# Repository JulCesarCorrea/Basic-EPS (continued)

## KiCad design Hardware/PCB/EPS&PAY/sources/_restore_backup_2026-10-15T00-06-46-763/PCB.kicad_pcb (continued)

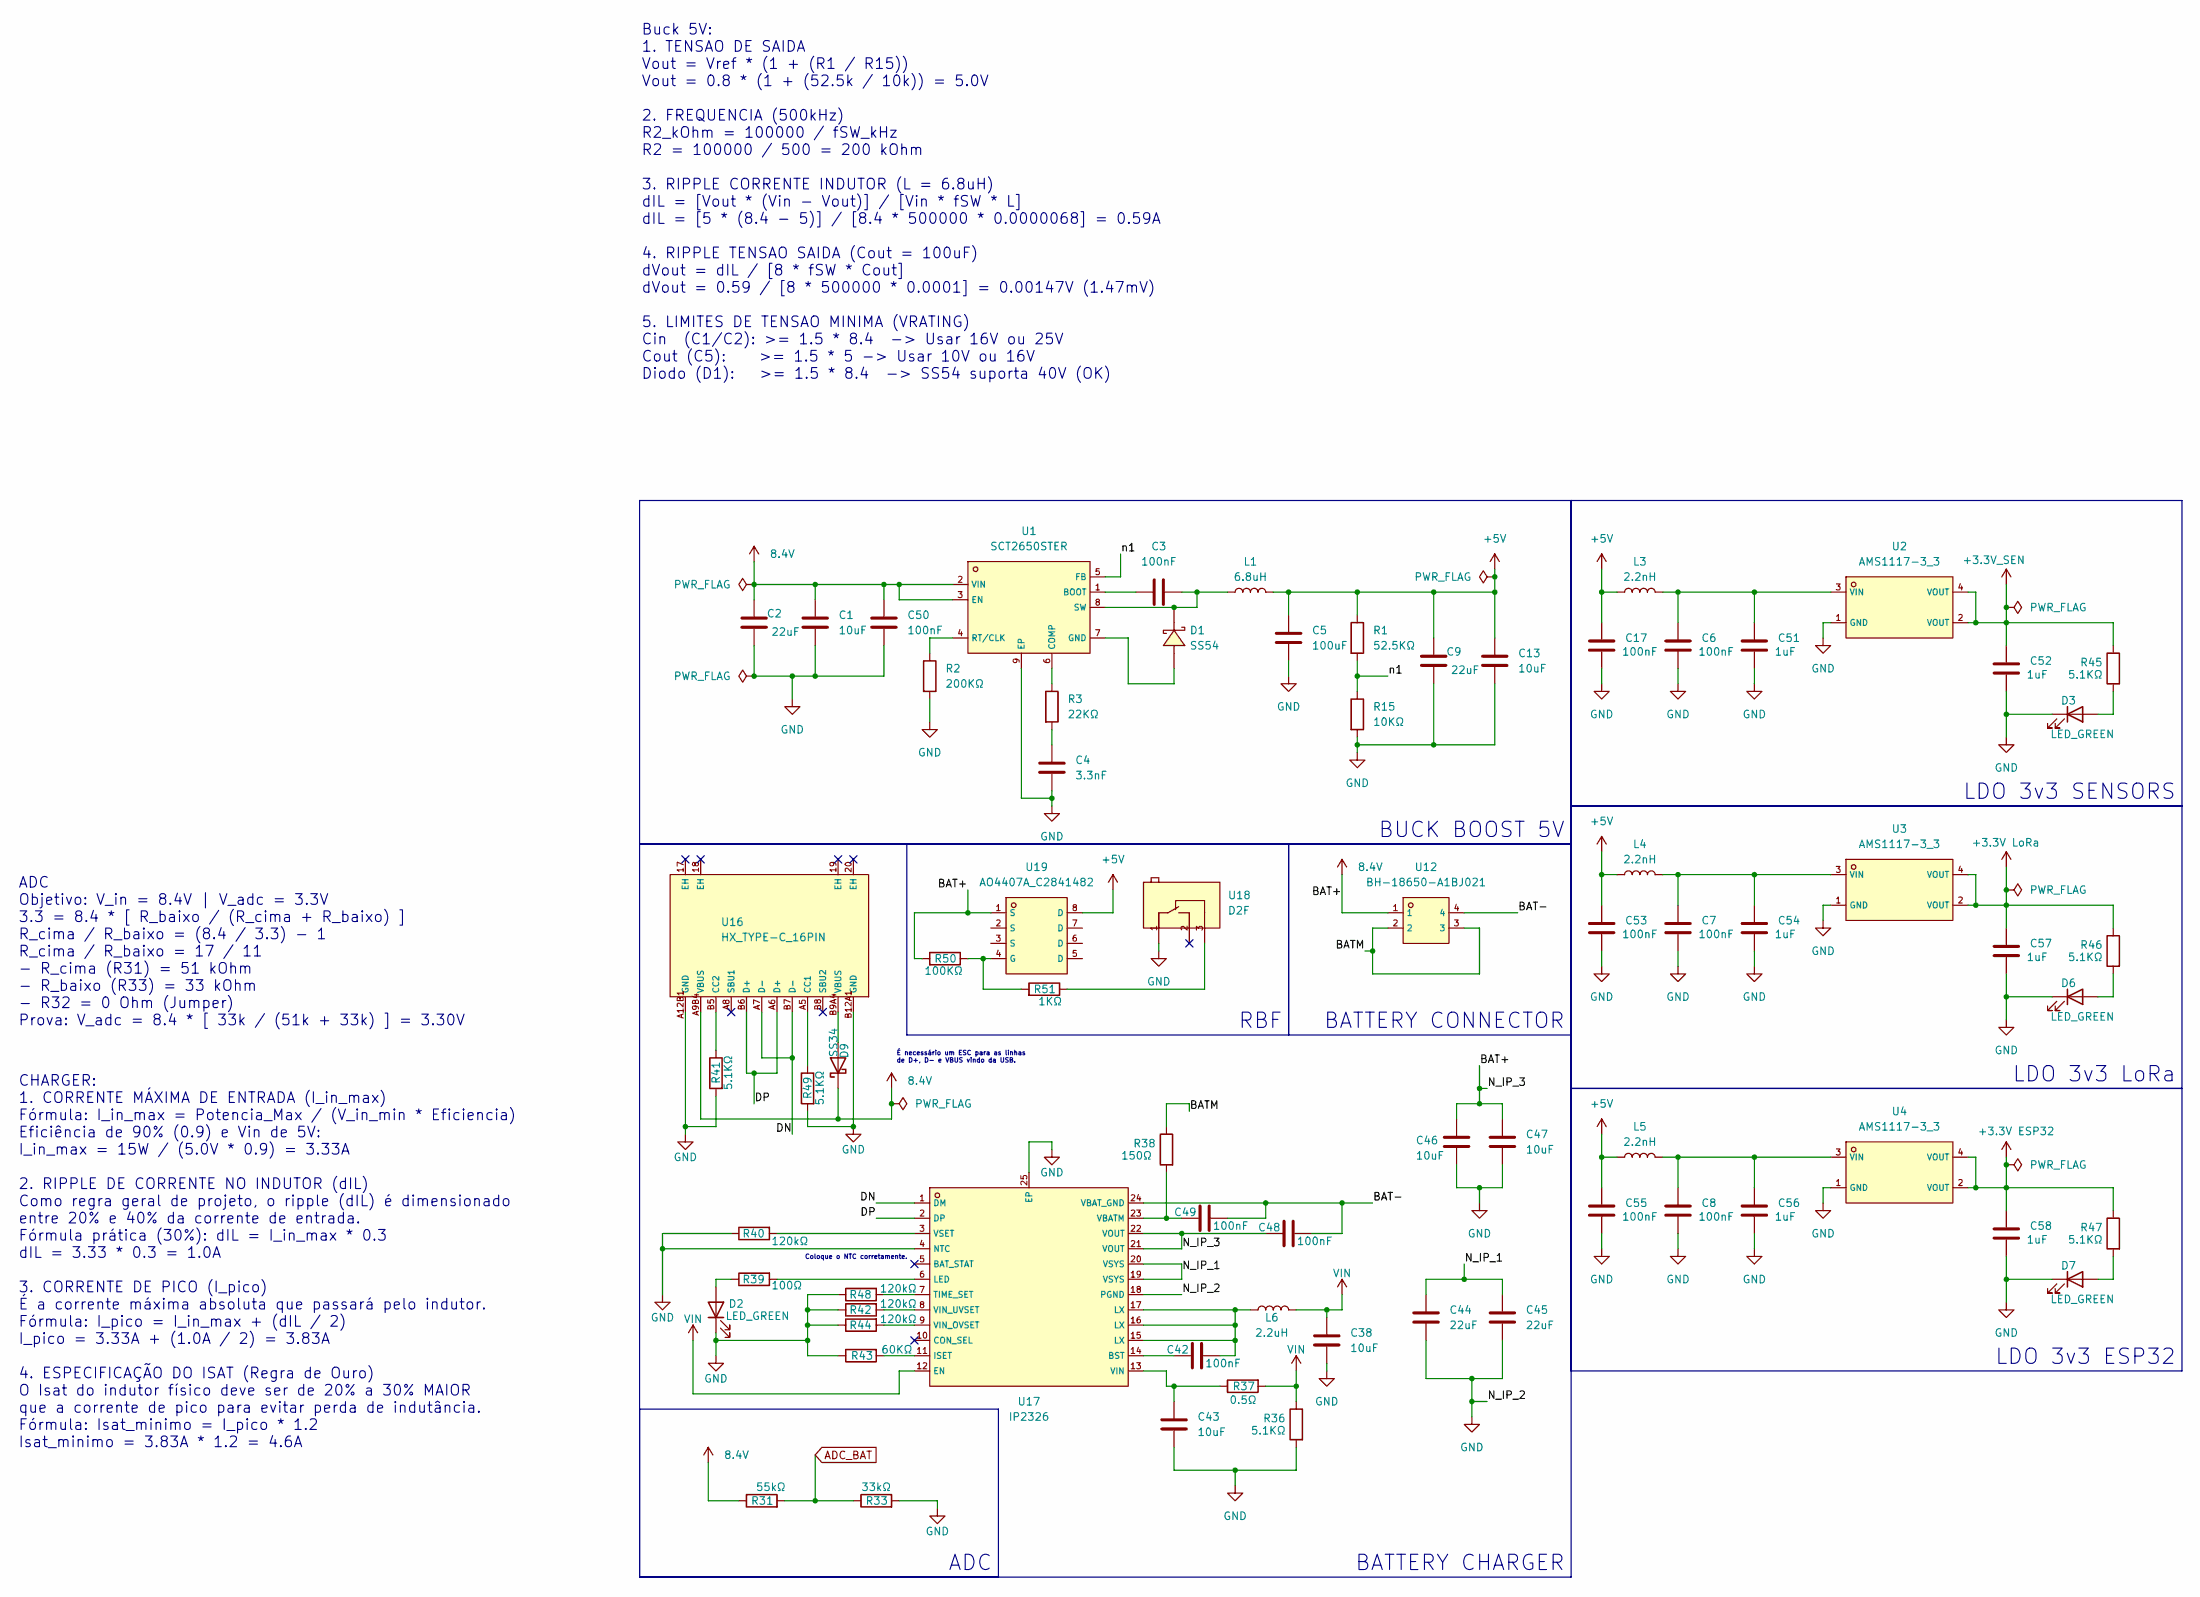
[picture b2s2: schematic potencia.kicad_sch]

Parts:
C1, C13, C38, C43, C46, C47: 10uF; C0805; LCSC C440198
C2, C9, C44, C45: 22uF; C1206; LCSC C3038553
C3, C6, C7, C8, C17, C42, C48, C49, C50, C53, C55: 100nF; C0603; LCSC C14663
C4: 3.3nF; C0603; LCSC C1613
C5: 100uF; C1206; LCSC C3038553
C51, C52, C54, C56, C57, C58: 1uF; C0603; LCSC C5199872
D1: SS54; SMB_L4.3-W3.6-LS5.4-RD; LCSC C5200096
D2, D3, D6, D7: LED_GREEN; LED0603-FD; LCSC C19273151
D9: SS34; D_SMA
L1: 6.8uH; IND-SMD_L5.4-W5.2; LCSC C718382
L3, L4, L5: 2.2nH; L1008; LCSC C2041833
L6: 2.2uH; L1008; LCSC C42455362
R1: 52.5KΩ; R0402; LCSC C2998086
R2: 200KΩ; R0603; LCSC C2907009
R3: 22KΩ; R0603; LCSC C2907015
R15: 10KΩ; R0603; LCSC C98220
R31: 55kΩ; R_0603_1608Metric_Pad0.98x0.95mm_HandSolder; LCSC C2933461
R33: 33kΩ; R_1206_3216Metric_Pad1.30x1.75mm_HandSolder; LCSC C2933415
R36, R41, R45, R46, R47, R49: 5.1KΩ; R0603; LCSC C2907044
R37: 0.5Ω; RES-SMD_L6.4-W3.2-R2512; LCSC C2904268
R38: 150Ω; R0603; LCSC C2933324
R39: 100Ω; R0603; LCSC C2906981
R40, R42, R44, R48: 120kΩ; R0603; LCSC C25808
R43: 60KΩ; R0603; LCSC C2907044
R50: 100KΩ; R0603; LCSC C14675
R51: 1KΩ; R0603; LCSC C22548
U1: SCT2650STER; ESOP-8_L4.9-W3.9-P1.27-LS6.0-BL-EP-2; LCSC C2840771
U2, U3, U4: AMS1117-3_3; SOT-223-3_L6.5-W3.4-P2.30-LS7.0-BR; LCSC C6186
U12: BH-18650-A1BJ021; BAT-TH_L77.0-W39.9_BH-18650-A1BJ021; LCSC C20606804
U16: HX_TYPE-C_16PIN; TYPE-C-SMD_HX-TYPE-C-16PIN; LCSC C5178539
U17: IP2326; VQFN-24_L4.0-W4.0-P0.50-BL-EP2.5; LCSC C2832094
U18: D2F; SW-TH_D2F-L; LCSC C397279
U19: AO4407A_C2841482; SOP-8_L5.0-W4.0-P1.27-LS6.0-BL; LCSC C2841482

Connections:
8.4V: C1.1, C2.1, C46.1, C47.1, C48.2, C50.2, D9.1 (K), R31.1, R50.2, U1.2 (VIN), U1.3 (EN), U12.1, U16.A9B4 (VBUS), U17.21 (VOUT), U17.22 (VOUT), U19.1 (S)
+3.3V ESP32: C58.2, R47.1, U4.2 (VOUT), U4.4 (VOUT); also elsewhere on the board
+3.3V LoRa: C57.2, R46.1, U3.2 (VOUT), U3.4 (VOUT); also elsewhere on the board
+3.3V_SEN: C52.2, R45.1, U2.2 (VOUT), U2.4 (VOUT); also elsewhere on the board
+5V: C5.1, C9.1, C13.1, C17.2, C53.2, C55.2, L1.2, L3.1, L4.1, L5.1, R1.1, U19.8 (D); also elsewhere on the board
/Potência/BAT-: C48.1, C49.1, U12.4, U17.24 (VBAT_GND)
/Potência/BATM: R38.1, U12.2, U12.3
/Potência/DN: U16.A7 (D-), U16.B7 (D-), U17.1 (DM)
/Potência/DP: U16.A6 (D+), U16.B6 (D+), U17.2 (DP)
/Potência/N_IP_1: C44.1, C45.1, U17.19 (VSYS), U17.20 (VSYS)
/Potência/n1: R1.2, R15.1, U1.5 (FB)
ADC_BAT: R31.2, R33.1; also elsewhere on the board
GND: C1.2, C2.2, C4.2, C5.2, C6.1, C7.1, C8.1, C9.2, C13.2, C17.1, C38.2, C43.2, C44.2, C45.2, C46.2, C47.2, C50.1, C51.1, C52.1, C53.1, C54.1, C55.1, C56.1, C57.1, C58.1, D2.1 (K), D3.1 (K), D6.1 (K), D7.1 (K), R2.2, R15.2, R33.2, R36.2, R40.1, R41.2, R42.1, R43.1, R44.1, R48.1, R49.2, U1.9 (EP), U2.1 (GND), U3.1 (GND), U4.1 (GND), U16.A12B1 (GND), U16.B12A1 (GND), U17.4 (NTC), U17.18 (PGND), U17.25 (EP), U18.1 (COM); also elsewhere on the board
unnamed: C4.1, R3.2
unnamed: C42.1, L6.1, U17.15 (LX), U17.16 (LX), U17.17 (LX)
unnamed: D2.2 (A), R39.1
unnamed: D3.2 (A), R45.2
unnamed: D6.2 (A), R46.2
unnamed: D7.2 (A), R47.2
unnamed: D9.2 (A), U16.B9A4 (VBUS)
unnamed: C3.1, U1.1 (BOOT)
unnamed: R3.1, U1.6 (COMP)
unnamed: D1.2, U1.7 (GND)
unnamed: R2.1, U1.4 (RT/CLK)
unnamed: C3.2, D1.1, L1.1, U1.8 (SW)
unnamed: C6.2, C51.2, L3.2, U2.3 (VIN)
unnamed: C7.2, C54.2, L4.2, U3.3 (VIN)
unnamed: C8.2, C56.2, L5.2, U4.3 (VIN)
unnamed: R49.1, U16.A5 (CC1)
unnamed: R41.1, U16.B5 (CC2)
unnamed: C42.2, U17.14 (BST)
unnamed: R43.2, U17.11 (ISET)
unnamed: R39.2, U17.6 (LED)
unnamed: R48.2, U17.7 (TIME_SET)
unnamed: C49.2, R38.2, U17.23 (VBATM)
unnamed: C43.1, R37.1, U17.13 (VIN)
unnamed: R44.2, U17.9 (VIN_OVSET)
unnamed: R42.2, U17.8 (VIN_UVSET)
unnamed: R40.2, U17.3 (VSET)
unnamed: R51.1, U18.3 (NC)
unnamed: R50.1, R51.2, U19.4 (G)
VIN: C38.1, L6.2, R36.1, R37.2, U17.12 (EN)

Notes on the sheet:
Coloque o NTC corretamente.
Buck 5V: 1. TENSAO DE SAIDA Vout = Vref * (1 + (R1 / R15)) Vout = 0.8 * (1 + (52.5k / 10k)) = 5.0V 2. FREQUENCIA (500kHz) R2_kOhm = 100000 / fSW_kHz R2 = 100000 / 500 = 200 kOhm 3. RIPPLE CORRENTE INDUTOR (L = 6.8uH) dIL = [Vout * (Vin - Vout)] / [Vin * fSW * L] dIL = [5 * (8.4 - 5)] / [8.4 * 50000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
ADC Objetivo: V_in = 8.4V | V_adc = 3.3V 3.3 = 8.4 * [ R_baixo / (R_cima + R_baixo) ] R_cima / R_baixo = (8.4 / 3.3) - 1 R_cima / R_baixo = 17 / 11 - R_cima (R31) = 51 kOhm - R_baixo (R33) = 33 kOhm - R32 = 0 Ohm (Jumper) Prova: V_adc = 8.4 * [ 33k / (51k + 33k) ] = 3.30V
CHARGER: 1. CORRENTE MÁXIMA DE ENTRADA (I_in_max) Fórmula: I_in_max = Potencia_Max / (V_in_min * Eficiencia) Eficiência de 90% (0.9) e Vin de 5V: I_in_max = 15W / (5.0V * 0.9) = 3.33A 2. RIPPLE DE CORRENTE NO INDUTOR (dIL) Como regra geral de projeto, o ripple (dIL) é dimensionado entre 20% e 40% d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
É necessário um ESC para as linhas de D+, D- e VBUS vindo da USB.
BATTERY CONNECTOR
LDO 3v3 SENSORS
ADC
LDO 3v3 LoRa
LDO 3v3 ESP32
BATTERY CHARGER
BUCK BOOST 5V
RBF

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
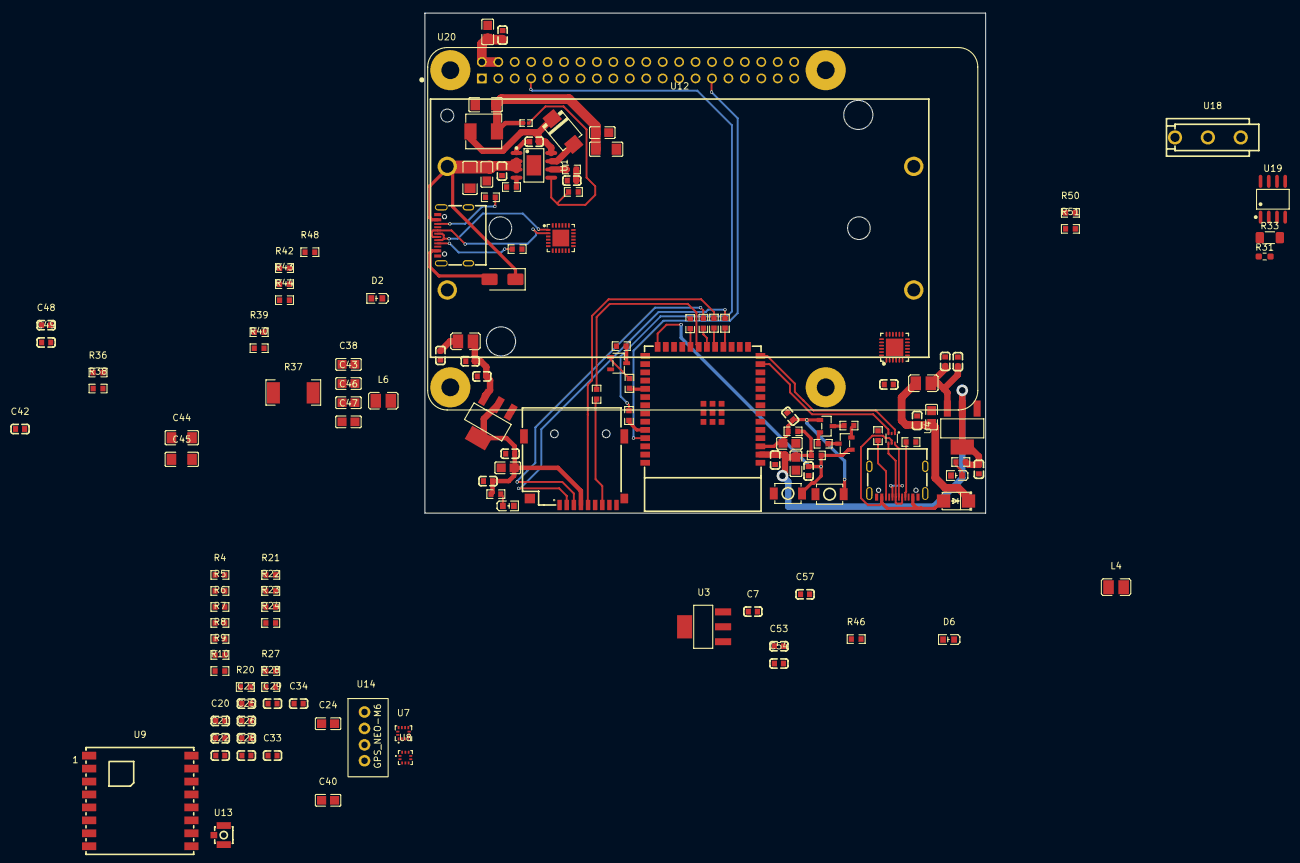
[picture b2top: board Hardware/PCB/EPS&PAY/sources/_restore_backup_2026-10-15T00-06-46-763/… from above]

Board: 2 copper layers, 86.6 x 77.2 mm, 139 parts (0 on the bottom side), 98 nets.
